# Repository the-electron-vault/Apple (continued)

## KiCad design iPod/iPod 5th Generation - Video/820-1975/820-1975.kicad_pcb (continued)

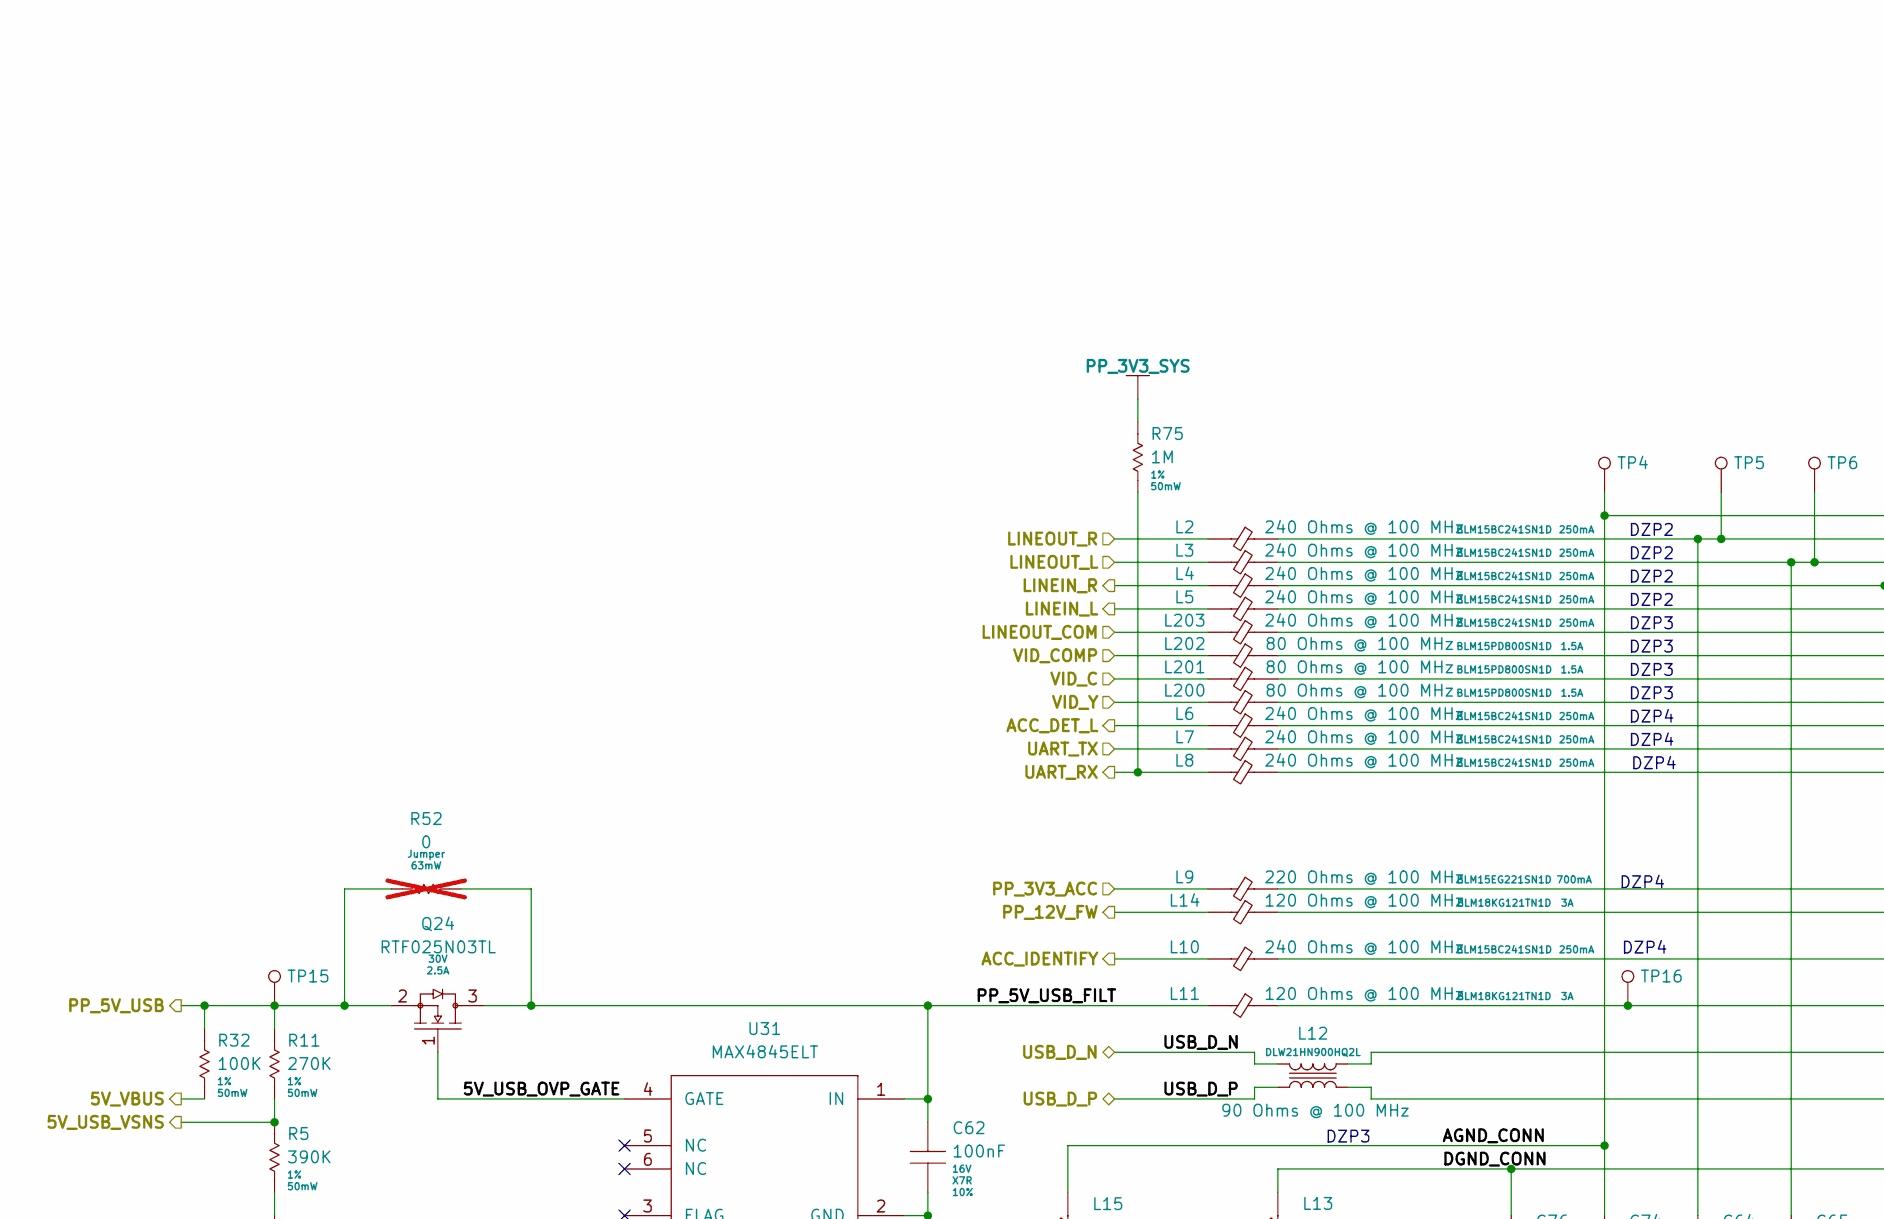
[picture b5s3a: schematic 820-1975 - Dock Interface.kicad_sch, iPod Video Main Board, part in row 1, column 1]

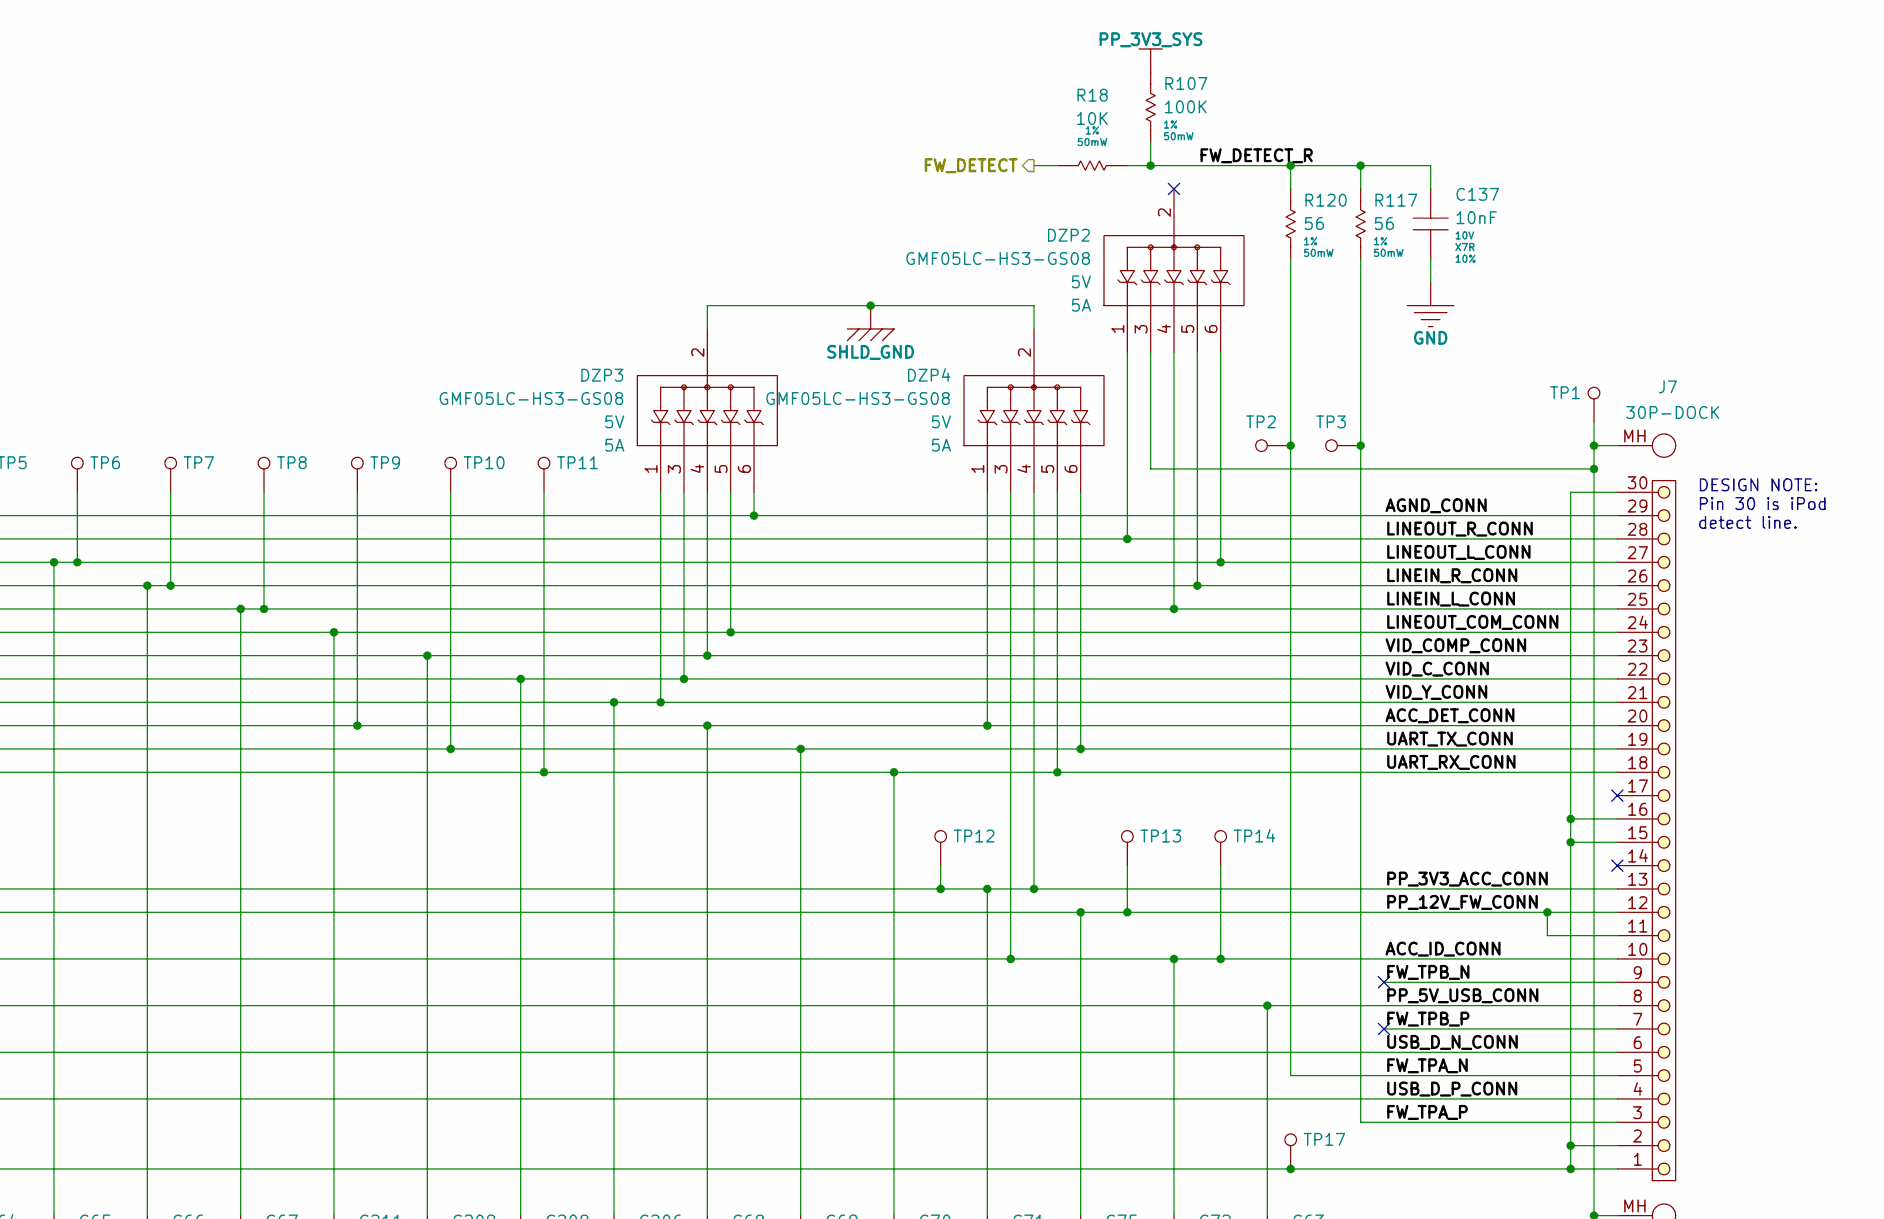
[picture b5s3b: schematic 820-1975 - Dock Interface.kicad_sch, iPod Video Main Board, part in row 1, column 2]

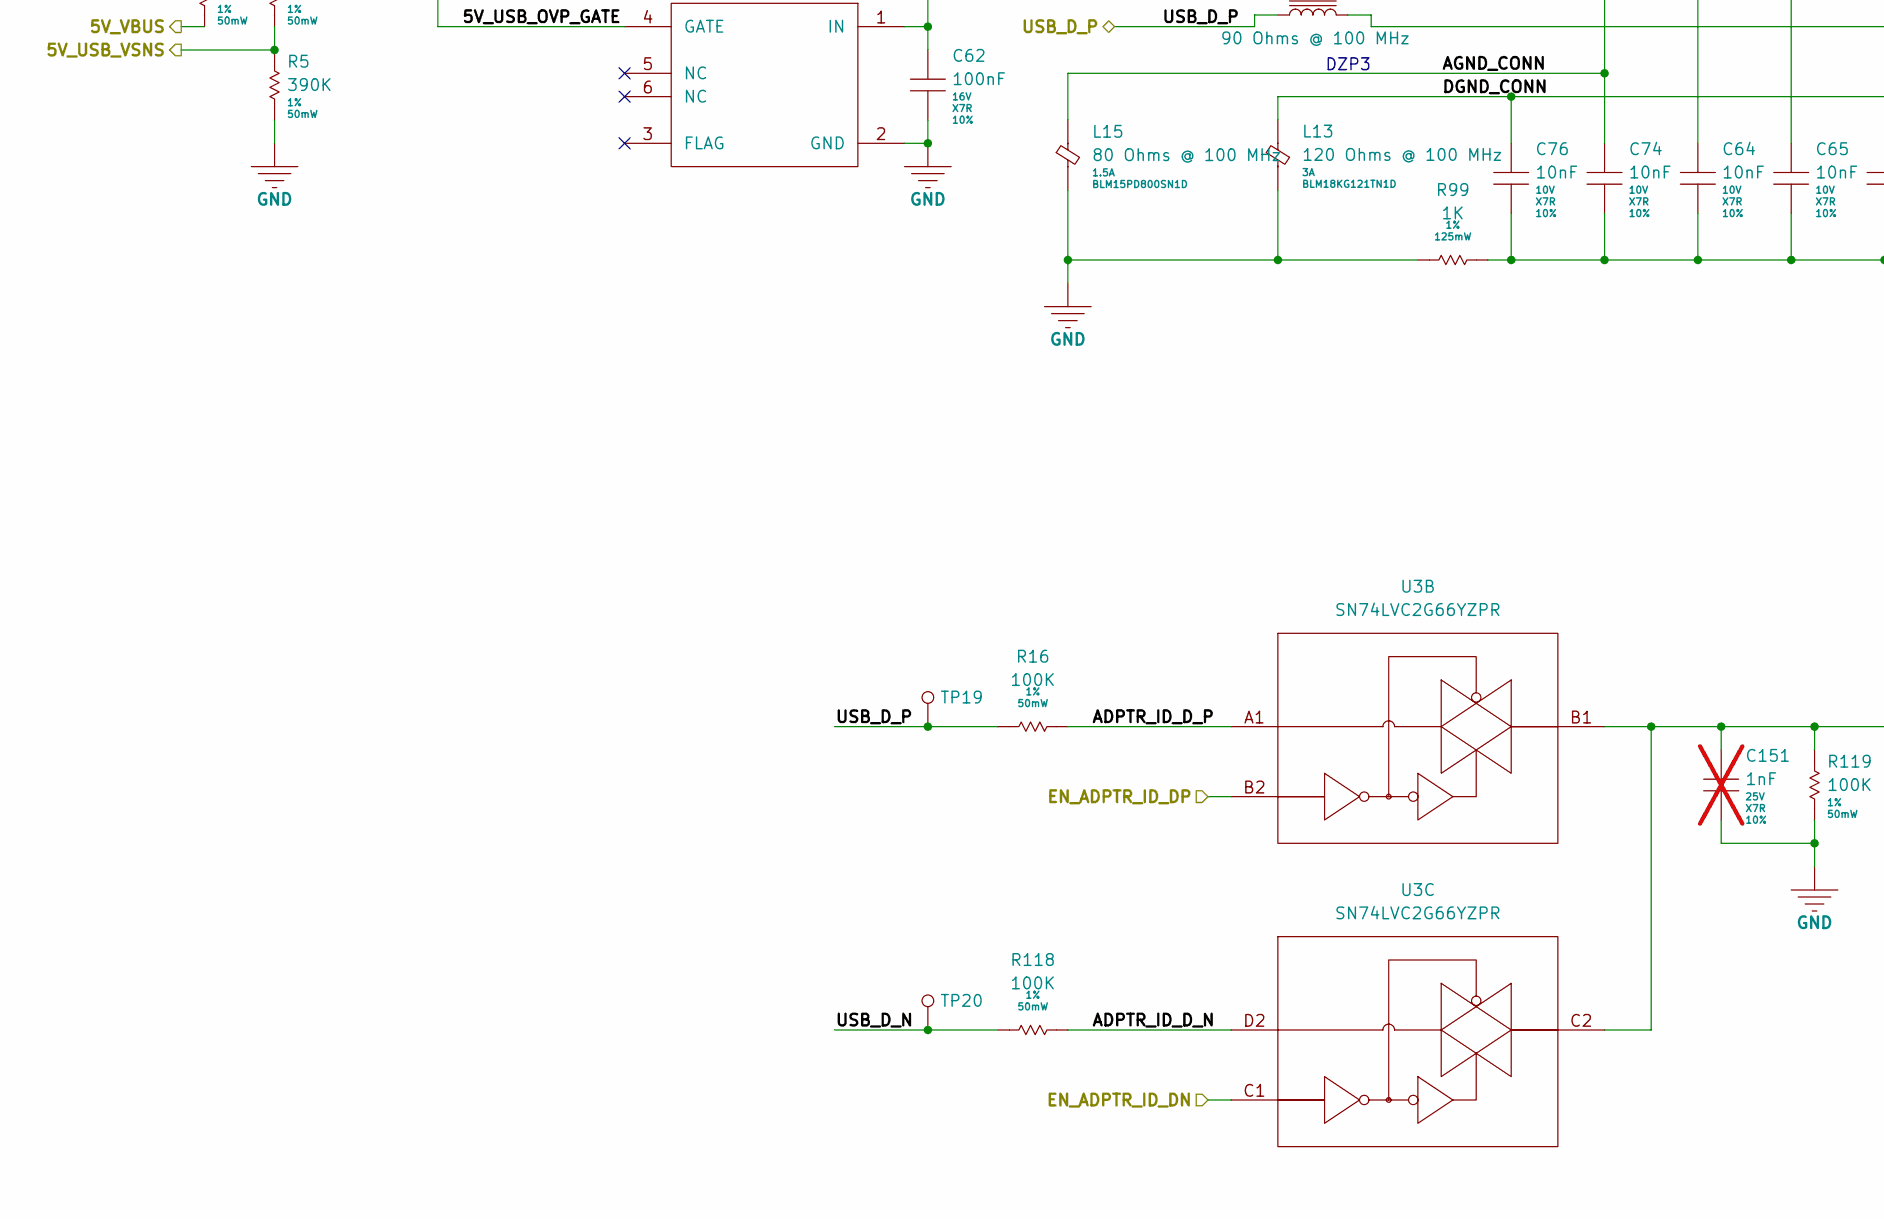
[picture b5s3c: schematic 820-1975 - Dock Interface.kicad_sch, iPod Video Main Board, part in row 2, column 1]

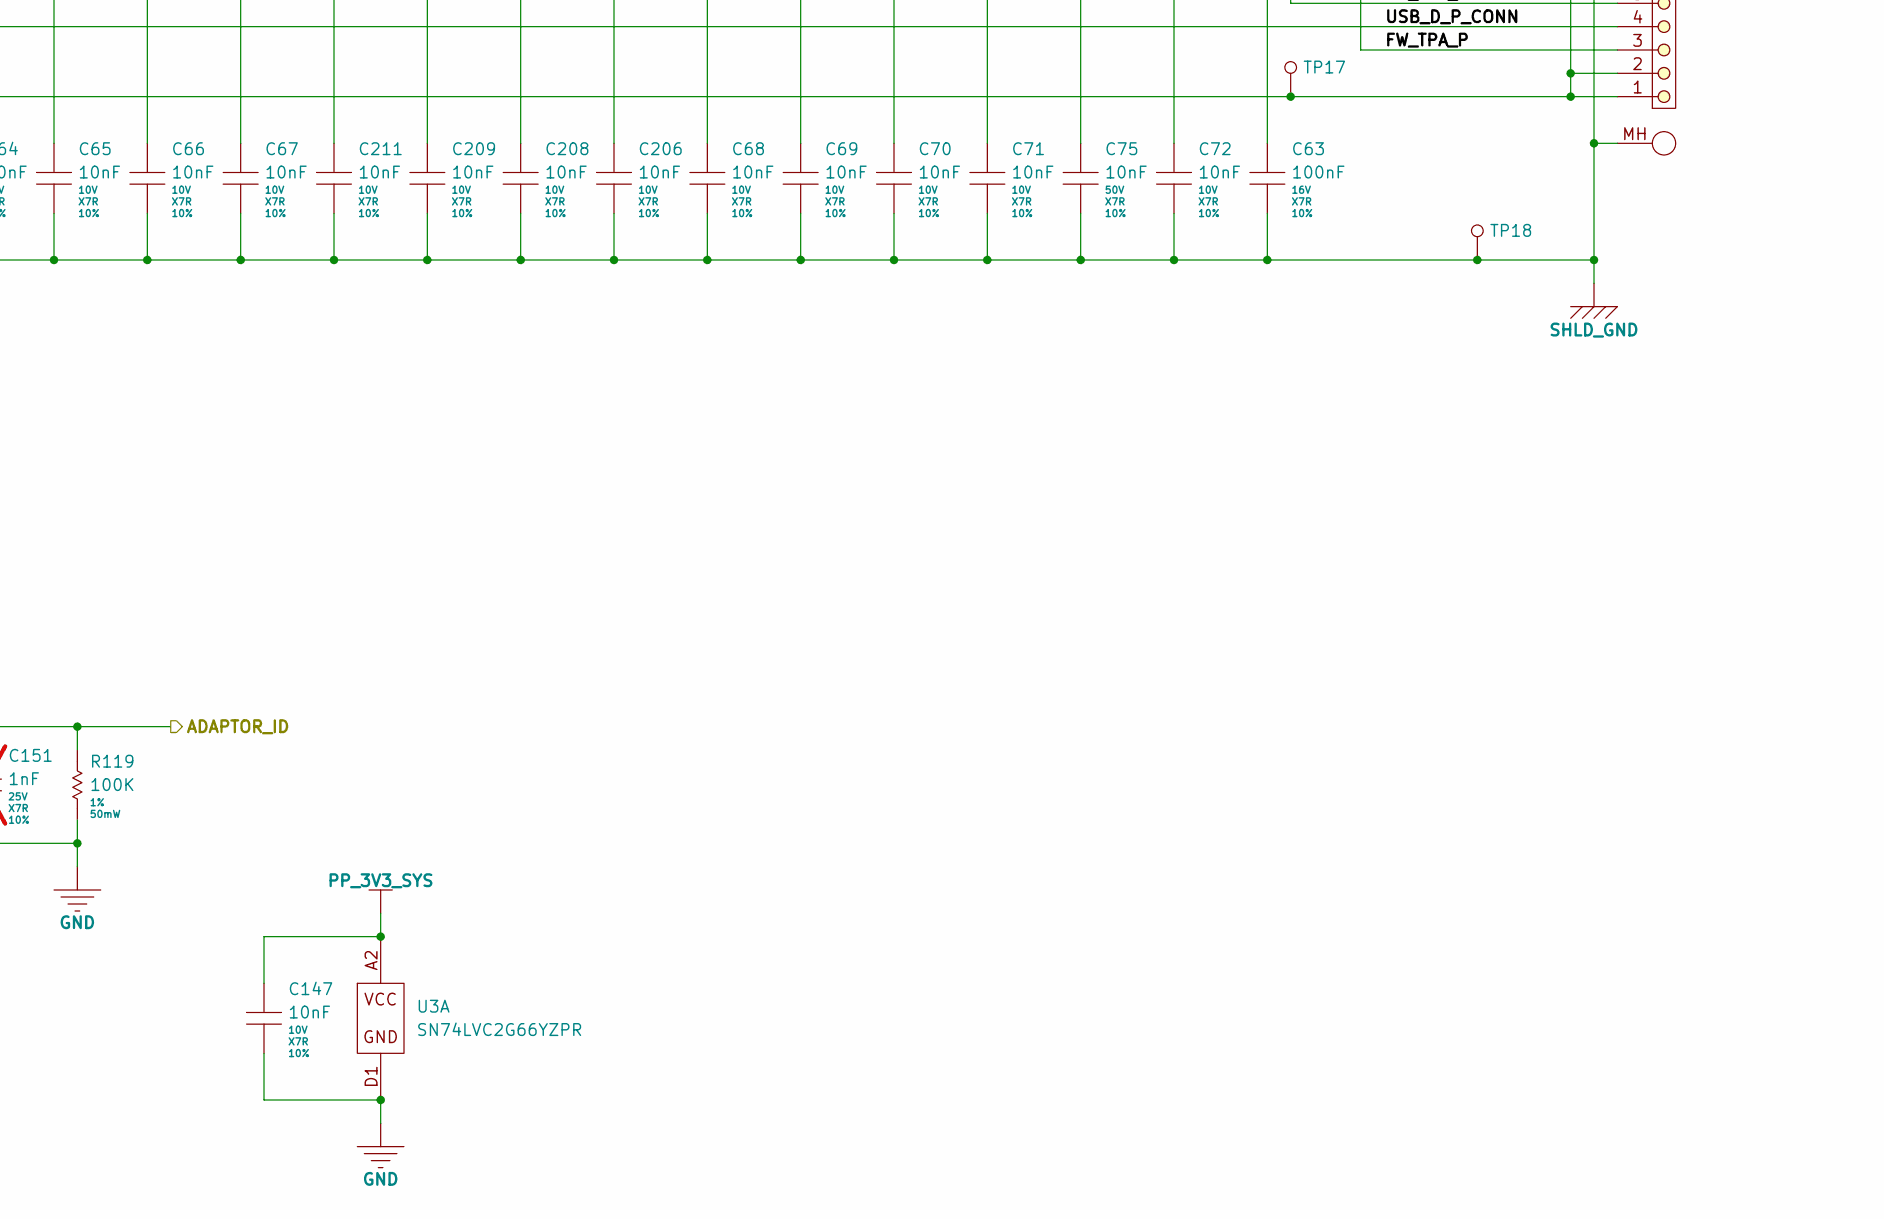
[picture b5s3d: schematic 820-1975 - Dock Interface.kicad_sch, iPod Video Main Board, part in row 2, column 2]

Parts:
C62, C63: 100nF; MLCC-0402; Voltage 16V; Tolerance 10%; Manufacturer Part Number GCM155R71C104KA55J
C64, C65, C66, C67, C68, C69, C70, C71, C72, C74, C76, C137, C147, C206, C208, C209, C211: 10nF; MLCC-0201; Voltage 10V; Tolerance 10%; Manufacturer Part Number GRM033R71A103KA01D
C75: 10nF; MLCC-0603; Voltage 50V; Tolerance 10%; Manufacturer Part Number GCM188R71H103KA37D
C151: 1nF; MLCC-0201; Voltage 25V; Tolerance 10%; Manufacturer Part Number GRM033R71E102KA01J; not fitted
DZP2, DZP3, DZP4: GMF05LC-HS3-GS08; VISHAY-LLP75-6A; Voltage 5V; Manufacturer Part Number GMF05LC-HS3-GS08
J7: 30P-DOCK; Manufacturer Part Number 30P-DOCK
L2, L3, L4, L5, L6, L7, L8, L10, L203: 240 Ohms @ 100 MHz; FB-0402; Manufacturer Part Number BLM15BC241SN1D
L9: 220 Ohms @ 100 MHz; FB-0402; Manufacturer Part Number BLM15EG221SN1D
L11, L13, L14: 120 Ohms @ 100 MHz; FB-0603; Manufacturer Part Number BLM18KG121TN1D
L12: 90 Ohms @ 100 MHz; DLW21HNxxxHQ; Manufacturer Part Number DLW21HN900HQ2L
L15, L200, L201, L202: 80 Ohms @ 100 MHz; FB-0402; Manufacturer Part Number BLM15PD800SN1D
Q24: RTF025N03TL; ROHM-SOT-323T; Voltage 30V; Manufacturer Part Number RTF025N03TL
R5: 390K; RES-0201; Tolerance 1%; Manufacturer Part Number CRCW0201390KFNED
R11: 270K; RES-0201; Tolerance 1%; Manufacturer Part Number CRCW0201270KFNED
R16, R32, R107, R118, R119: 100K; RES-0201; Tolerance 1%; Manufacturer Part Number CRCW0201100KFNED
R18: 10K; RES-0201; Tolerance 1%; Manufacturer Part Number CRCW020110K0FNED
R52: 0; RES-0402; Tolerance Jumper; Manufacturer Part Number CRCW04020000Z0ED; not fitted
R75: 1M; RES-0201; Tolerance 1%; Manufacturer Part Number CRCW02011M00FNED
R99: 1K; RES-0402; Tolerance 1%; Manufacturer Part Number CRCW04021K00FKED
R117, R120: 56; RES-0201; Tolerance 1%; Manufacturer Part Number CRCW020156R0FNED
TP1, TP2, TP3, TP4, TP5, TP6, TP7, TP8, TP9, TP10, TP11, TP12, TP13, TP14, TP15, TP16, TP17, TP18, TP19, TP20: TP; TP-SMT
U3: SN74LVC2G66YZPR; TI-R-XBGA-N8; Manufacturer Part Number SN74LVC2G66YZPR
U31: MAX4845ELT; MAXIM-6-uDFN; Manufacturer Part Number MAX4845ELT

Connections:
/CODEC/LINEIN_L: L4.1; also elsewhere on the board
/CODEC/LINEIN_R: L5.1; also elsewhere on the board
/CODEC/LINEOUT_COM: L203.1; also elsewhere on the board
/CODEC/LINEOUT_L: L3.1; also elsewhere on the board
/CODEC/LINEOUT_R: L2.1; also elsewhere on the board
/Charger-and-3.3V-Supply/PP_5V_USB: Q24.2 (S), R11.1, R32.1, R52.1, TP15.1; also elsewhere on the board
/Dock-Interface/5V_USB_OVP_GATE: Q24.1 (G), U31.4 (GATE)
/Dock-Interface/5V_USB_VSNS: R5.1, R11.2; also elsewhere on the board
/Dock-Interface/5V_VBUS: R32.2; also elsewhere on the board
/Dock-Interface/ACC_DET_CONN: C68.1, DZP4.1 (K1), J7.20, L6.2, TP9.1
/Dock-Interface/ACC_DET_L: L6.1; also elsewhere on the board
/Dock-Interface/ACC_IDENTIFY: L10.1; also elsewhere on the board
/Dock-Interface/ACC_ID_CONN: C72.1, DZP4.3 (K2), J7.10, L10.2, TP14.1
/Dock-Interface/ADAPTOR_ID: C151.1, R119.1, U3.B1 (1B), U3.C2 (2B); also elsewhere on the board
/Dock-Interface/ADPTR_ID_D_N: R118.2, U3.D2 (2A)
/Dock-Interface/ADPTR_ID_D_P: R16.2, U3.A1 (1A)
/Dock-Interface/AGND_CONN: C74.1, DZP3.6 (K5), J7.29, L15.2, TP4.1
/Dock-Interface/DGND_CONN: C76.1, J7.1, J7.2, J7.15, J7.16, J7.30, L13.1, TP17.1
/Dock-Interface/EN_ADPTR_ID_DN: U3.C1 (2C); also elsewhere on the board
/Dock-Interface/EN_ADPTR_ID_DP: U3.B2 (1C); also elsewhere on the board
/Dock-Interface/FW_DETECT: R18.1; also elsewhere on the board
/Dock-Interface/FW_DETECT_R: C137.1, R18.2, R107.2, R117.1, R120.1
/Dock-Interface/FW_TPA_N: J7.5, R120.2, TP2.1
/Dock-Interface/FW_TPA_P: J7.3, R117.2, TP3.1
/Dock-Interface/FW_TPB_N: J7.9
/Dock-Interface/FW_TPB_P: J7.7
/Dock-Interface/LINEIN_L_CONN: C67.1, DZP2.4 (K3), J7.25, L5.2, TP8.1
/Dock-Interface/LINEIN_R_CONN: C66.1, DZP2.5 (K4), J7.26, L4.2, TP7.1
/Dock-Interface/LINEOUT_COM_CONN: C211.1, DZP3.5 (K4), J7.24, L203.2
/Dock-Interface/LINEOUT_L_CONN: C65.1, DZP2.6 (K5), J7.27, L3.2, TP6.1
/Dock-Interface/LINEOUT_R_CONN: C64.1, DZP2.1 (K1), J7.28, L2.2, TP5.1
/Dock-Interface/PP_3V3_ACC: L9.1; also elsewhere on the board
/Dock-Interface/PP_3V3_ACC_CONN: C71.1, DZP4.4 (K3), J7.13, L9.2, TP12.1
/Dock-Interface/PP_5V_USB_CONN: C63.1, J7.8, L11.2, TP16.1
/Dock-Interface/PP_5V_USB_FILT: C62.1, L11.1, Q24.3 (D), R52.2, U31.1 (IN)
/Dock-Interface/PP_12V_FW: L14.1; also elsewhere on the board
/Dock-Interface/PP_12V_FW_CONN: C75.1, J7.11, J7.12, L14.2, TP13.1
/Dock-Interface/UART_RX: L8.1, R75.2; also elsewhere on the board
/Dock-Interface/UART_RX_CONN: C70.1, DZP4.5 (K4), J7.18, L8.2, TP11.1
/Dock-Interface/UART_TX: L7.1; also elsewhere on the board
/Dock-Interface/UART_TX_CONN: C69.1, DZP4.6 (K5), J7.19, L7.2, TP10.1
/Dock-Interface/USB_D_N: L12.1, R118.1, TP20.1; also elsewhere on the board
/Dock-Interface/USB_D_N_CONN: J7.6, L12.2
/Dock-Interface/USB_D_P: L12.4, R16.1, TP19.1; also elsewhere on the board
/Dock-Interface/USB_D_P_CONN: J7.4, L12.3
/Dock-Interface/VID_C: L201.1; also elsewhere on the board
/Dock-Interface/VID_COMP: L202.1; also elsewhere on the board
/Dock-Interface/VID_COMP_CONN: C209.1, DZP3.4 (K3), J7.23, L202.2
/Dock-Interface/VID_C_CONN: C208.1, DZP3.3 (K2), J7.22, L201.2
/Dock-Interface/VID_Y: L200.1; also elsewhere on the board
/Dock-Interface/VID_Y_CONN: C206.1, DZP3.1 (K1), J7.21, L200.2
GND: C62.2, C137.2, C147.2, C151.2, L13.2, L15.1, R5.2, R99.1, R119.2, U3.D1 (GND), U31.2 (GND); also elsewhere on the board
PP_3V3_SYS: C147.1, R75.1, R107.1, U3.A2 (VCC); also elsewhere on the board
SHLD_GND: C63.2, C64.2, C65.2, C66.2, C67.2, C68.2, C69.2, C70.2, C71.2, C72.2, C74.2, C75.2, C76.2, C206.2, C208.2, C209.2, C211.2, DZP2.3 (K2), DZP3.2 (A), DZP4.2 (A), J7.MH, R99.2, TP1.1, TP18.1

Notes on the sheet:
DESIGN NOTE: Pin 30 is iPod detect line.
DZP2
DZP4
DZP3

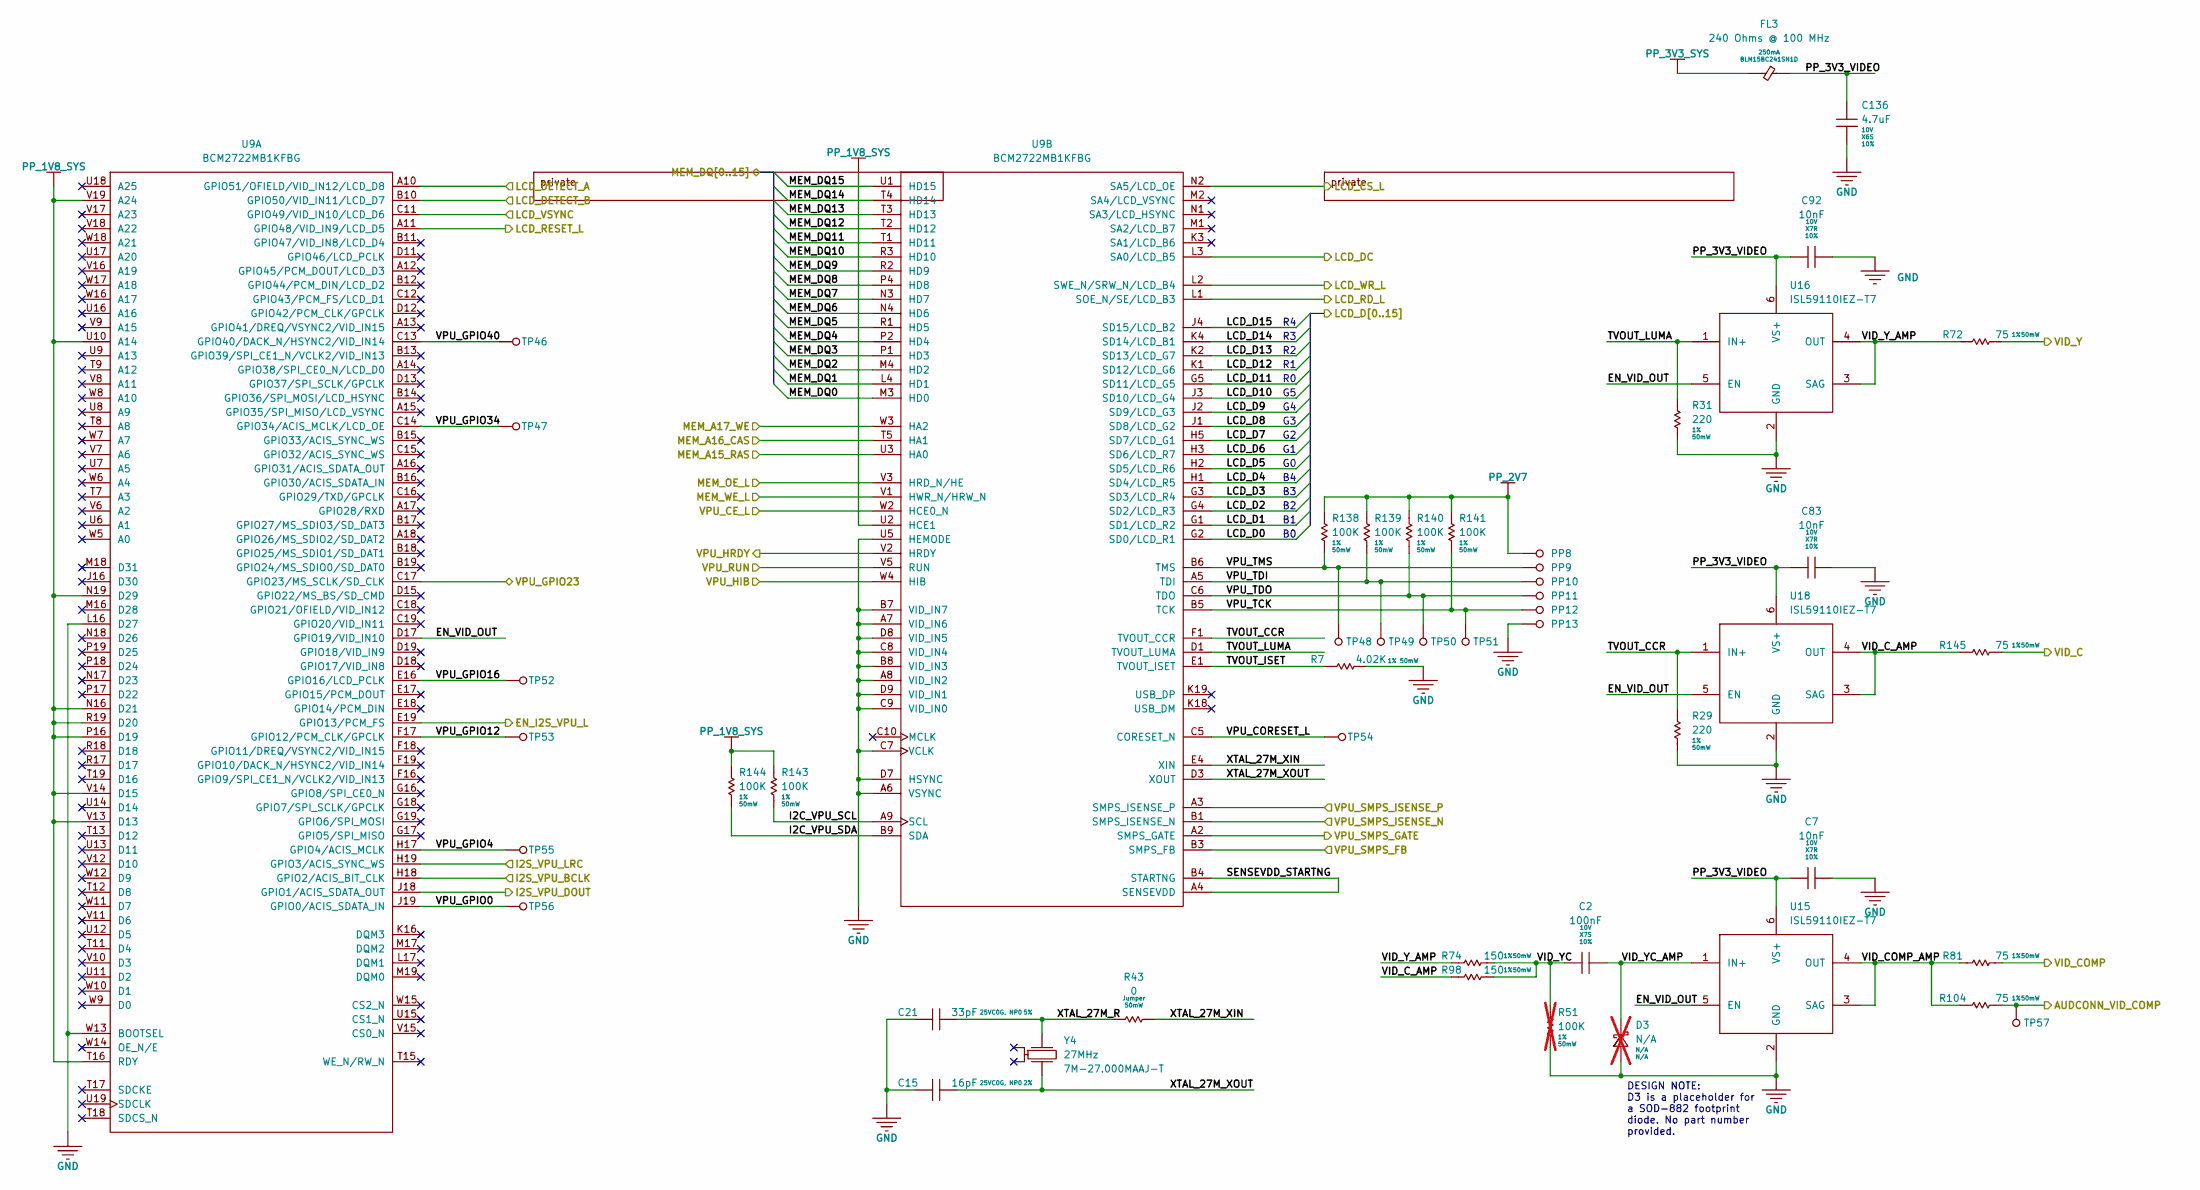
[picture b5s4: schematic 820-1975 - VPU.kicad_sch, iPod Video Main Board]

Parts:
C2: 100nF; MLCC-0201; Voltage 10V; Tolerance 10%; Manufacturer Part Number GRM033C71A104KE14D
C7, C83, C92: 10nF; MLCC-0201; Voltage 10V; Tolerance 10%; Manufacturer Part Number GRM033R71A103KA01D
C15: 16pF; MLCC-0201; Voltage 25V; Tolerance 2%; Manufacturer Part Number GRM0335C1E160GA01D
C21: 33pF; MLCC-0201; Voltage 25V; Tolerance 5%; Manufacturer Part Number GRM0335C1E330JA01D
C136: 4.7uF; MLCC-0603; Voltage 10V; Tolerance 10%; Manufacturer Part Number GRM188C71A475KE11D
D3: N/A; SOD-882; Voltage N/A; Manufacturer Part Number N/A; not fitted
FL3: 240 Ohms @ 100 MHz; FB-0402; Manufacturer Part Number BLM15BC241SN1D
PP8, PP9, PP10, PP11, PP12, PP13: TP; TP-SMT
R7: 4.02K; RES-0201; Tolerance 1%; Manufacturer Part Number CRCW02014K02FNED
R29, R31: 220; RES-0201; Tolerance 1%; Manufacturer Part Number CRCW0201220RFKED
R43: 0; RES-0201; Tolerance Jumper; Manufacturer Part Number CRCW02010000Z0ED
R51: 100K; RES-0201; Tolerance 1%; Manufacturer Part Number CRCW0201100KFNED; not fitted
R72, R81, R104, R145: 75; RES-0201; Tolerance 1%; Manufacturer Part Number CRCW020175R0FNED
R74, R98: 150; RES-0201; Tolerance 1%; Manufacturer Part Number CRCW0201150RFKED
R138, R139, R140, R141, R143, R144: 100K; RES-0201; Tolerance 1%; Manufacturer Part Number CRCW0201100KFNED
TP46, TP47, TP48, TP49, TP50, TP51, TP52, TP53, TP54, TP55, TP56, TP57: TP; TP-SMT
U9: BCM2722MB1KFBG; Manufacturer Part Number BCM2722MB1KFBG
U15, U16, U18: ISL59110IEZ-T7; ISL59110IEZ; Manufacturer Part Number ISL59110IEZ-T7
Y4: 27MHz; XTAL-3.2x2.5; Tolerance 30ppm; Manufacturer Part Number 7M-27.000MAAJ-T

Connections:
/CODEC/AUDCONN_VID_COMP: R104.2, TP57.1; also elsewhere on the board
/CODEC/EN_I2S_VPU_L: U9.E19 (GPIO13/PCM_FS); also elsewhere on the board
/CODEC/I2S_VPU_BCLK: U9.H18 (GPIO2/ACIS_BIT_CLK); also elsewhere on the board
/CODEC/I2S_VPU_DOUT: U9.J18 (GPIO1/ACIS_SDATA_OUT); also elsewhere on the board
/CODEC/I2S_VPU_LRC: U9.H19 (GPIO3/ACIS_SYNC_WS); also elsewhere on the board
/Dock-Interface/VID_C: R145.2; also elsewhere on the board
/Dock-Interface/VID_COMP: R81.2; also elsewhere on the board
/Dock-Interface/VID_Y: R72.2; also elsewhere on the board
/Flash-and-SDRAM/MEM_A15_RAS: U9.U3 (HA0); also elsewhere on the board
/Flash-and-SDRAM/MEM_A16_CAS: U9.T5 (HA1); also elsewhere on the board
/Flash-and-SDRAM/MEM_A17_WE: U9.W3 (HA2); also elsewhere on the board
/Flash-and-SDRAM/MEM_DQ0: U9.M3 (HD0); also elsewhere on the board
/Flash-and-SDRAM/MEM_DQ1: U9.L4 (HD1); also elsewhere on the board
/Flash-and-SDRAM/MEM_DQ2: U9.M4 (HD2); also elsewhere on the board
/Flash-and-SDRAM/MEM_DQ3: U9.P1 (HD3); also elsewhere on the board
/Flash-and-SDRAM/MEM_DQ4: U9.P2 (HD4); also elsewhere on the board
/Flash-and-SDRAM/MEM_DQ5: U9.R1 (HD5); also elsewhere on the board
/Flash-and-SDRAM/MEM_DQ6: U9.N4 (HD6); also elsewhere on the board
/Flash-and-SDRAM/MEM_DQ7: U9.N3 (HD7); also elsewhere on the board
/Flash-and-SDRAM/MEM_DQ8: U9.P4 (HD8); also elsewhere on the board
/Flash-and-SDRAM/MEM_DQ9: U9.R2 (HD9); also elsewhere on the board
/Flash-and-SDRAM/MEM_DQ10: U9.R3 (HD10); also elsewhere on the board
/Flash-and-SDRAM/MEM_DQ11: U9.T1 (HD11); also elsewhere on the board
/Flash-and-SDRAM/MEM_DQ12: U9.T2 (HD12); also elsewhere on the board
/Flash-and-SDRAM/MEM_DQ13: U9.T3 (HD13); also elsewhere on the board
/Flash-and-SDRAM/MEM_DQ14: U9.T4 (HD14); also elsewhere on the board
/Flash-and-SDRAM/MEM_DQ15: U9.U1 (HD15); also elsewhere on the board
/Flash-and-SDRAM/MEM_OE_L: U9.V3 (HRD_N/HE); also elsewhere on the board
/Flash-and-SDRAM/MEM_WE_L: U9.V1 (HWR_N/HRW_N); also elsewhere on the board
/LCD/LCD_CS_L: U9.N2 (SA5/LCD_OE); also elsewhere on the board
/LCD/LCD_D0: U9.G2 (SD0/LCD_R1); also elsewhere on the board
/LCD/LCD_D1: U9.G1 (SD1/LCD_R2); also elsewhere on the board
/LCD/LCD_D2: U9.G4 (SD2/LCD_R3); also elsewhere on the board
/LCD/LCD_D3: U9.G3 (SD3/LCD_R4); also elsewhere on the board
/LCD/LCD_D4: U9.H1 (SD4/LCD_R5); also elsewhere on the board
/LCD/LCD_D5: U9.H2 (SD5/LCD_R6); also elsewhere on the board
/LCD/LCD_D6: U9.H3 (SD6/LCD_R7); also elsewhere on the board
/LCD/LCD_D7: U9.H5 (SD7/LCD_G1); also elsewhere on the board
/LCD/LCD_D8: U9.J1 (SD8/LCD_G2); also elsewhere on the board
/LCD/LCD_D9: U9.J2 (SD9/LCD_G3); also elsewhere on the board
/LCD/LCD_D10: U9.J3 (SD10/LCD_G4); also elsewhere on the board
/LCD/LCD_D11: U9.G5 (SD11/LCD_G5); also elsewhere on the board
/LCD/LCD_D12: U9.K1 (SD12/LCD_G6); also elsewhere on the board
/LCD/LCD_D13: U9.K2 (SD13/LCD_G7); also elsewhere on the board
/LCD/LCD_D14: U9.K4 (SD14/LCD_B1); also elsewhere on the board
/LCD/LCD_D15: U9.J4 (SD15/LCD_B2); also elsewhere on the board
/LCD/LCD_DC: U9.L3 (SA0/LCD_B5); also elsewhere on the board
/LCD/LCD_RD_L: U9.L1 (SOE_N/SE/LCD_B3); also elsewhere on the board
/LCD/LCD_RESET_L: U9.A11 (GPIO48/VID_IN9/LCD_D5); also elsewhere on the board
/LCD/LCD_VSYNC: U9.C11 (GPIO49/VID_IN10/LCD_D6); also elsewhere on the board
/LCD/LCD_WR_L: U9.L2 (SWE_N/SRW_N/LCD_B4); also elsewhere on the board
/LCD_DETECT_A: U9.A10 (GPIO51/OFIELD/VID_IN12/LCD_D8); also elsewhere on the board
/LCD_DETECT_B: U9.B10 (GPIO50/VID_IN11/LCD_D7); also elsewhere on the board
/MPU/VPU_CE_L: U9.W2 (HCE0_N); also elsewhere on the board
/MPU/VPU_GPIO23: U9.C17 (GPIO23/MS_SCLK/SD_CLK); also elsewhere on the board
/MPU/VPU_HIB: U9.W4 (HIB); also elsewhere on the board
/MPU/VPU_HRDY: U9.V2 (HRDY); also elsewhere on the board
/MPU/VPU_RUN: U9.V5 (RUN); also elsewhere on the board
/VPU-Power/VPU_SMPS_FB: U9.B3 (SMPS_FB); also elsewhere on the board
/VPU-Power/VPU_SMPS_GATE: U9.A2 (SMPS_GATE); also elsewhere on the board
/VPU-Power/VPU_SMPS_ISENSE_N: U9.B1 (SMPS_ISENSE_N); also elsewhere on the board
/VPU/EN_VID_OUT: U9.D17 (GPIO19/VID_IN10), U15.5 (EN), U16.5 (EN), U18.5 (EN)
/VPU/I2C_VPU_SCL: R143.2, U9.A9 (SCL)
/VPU/I2C_VPU_SDA: R144.2, U9.B9 (SDA)
/VPU/PP_3V3_VIDEO: C7.1, C83.1, C92.1, C136.1, FL3.2, U15.6 (VS+), U16.6 (VS+), U18.6 (VS+)
/VPU/SENSEVDD_STARTNG: U9.A4 (SENSEVDD), U9.B4 (STARTNG)
/VPU/TVOUT_CCR: R29.1, U9.F1 (TVOUT_CCR), U18.1 (IN+)
/VPU/TVOUT_ISET: R7.1, U9.E1 (TVOUT_ISET)
/VPU/TVOUT_LUMA: R31.1, U9.D1 (TVOUT_LUMA), U16.1 (IN+)
/VPU/VID_COMP_AMP: R81.1, R104.1, U15.3 (SAG), U15.4 (OUT)
/VPU/VID_C_AMP: R98.1, R145.1, U18.3 (SAG), U18.4 (OUT)
/VPU/VID_YC: C2.1, R51.1, R74.2, R98.2
/VPU/VID_YC_AMP: C2.2, D3.K, U15.1 (IN+)
/VPU/VID_Y_AMP: R72.1, R74.1, U16.3 (SAG), U16.4 (OUT)
/VPU/VPU_CORESET_L: TP54.1, U9.C5 (CORESET_N)
/VPU/VPU_GPIO0: TP56.1, U9.J19 (GPIO0/ACIS_SDATA_IN)
/VPU/VPU_GPIO4: TP55.1, U9.H17 (GPIO4/ACIS_MCLK)
/VPU/VPU_GPIO12: TP53.1, U9.F17 (GPIO12/PCM_CLK/GPCLK)
/VPU/VPU_GPIO16: TP52.1, U9.E16 (GPIO16/LCD_PCLK)
/VPU/VPU_GPIO34: TP47.1, U9.C14 (GPIO34/ACIS_MCLK/LCD_OE)
/VPU/VPU_GPIO40: TP46.1, U9.C13 (GPIO40/DACK_N/HSYNC2/VID_IN14)
/VPU/VPU_TCK: PP12.1, R141.2, TP51.1, U9.B5 (TCK)
/VPU/VPU_TDI: PP10.1, R139.2, TP49.1, U9.A5 (TDI)
/VPU/VPU_TDO: PP11.1, R140.2, TP50.1, U9.C6 (TDO)
/VPU/VPU_TMS: PP9.1, R138.2, TP48.1, U9.B6 (TMS)
/VPU/XTAL_27M_R: C21.1, R43.1, Y4.1
/VPU/XTAL_27M_XIN: R43.2, U9.E4 (XIN)
/VPU/XTAL_27M_XOUT: C15.1, U9.D3 (XOUT), Y4.3
GND: C7.2, C15.2, C21.2, C83.2, C92.2, C136.2, D3.A, PP13.1, R7.2, R29.2, R31.2, R51.2, U9.A6 (VSYNC), U9.A7 (VID_IN6), U9.A8 (VID_IN2), U9.B7 (VID_IN7), U9.B8 (VID_IN3), U9.C7 (VCLK), U9.C8 (VID_IN4), U9.C9 (VID_IN0), U9.D7 (HSYNC), U9.D8 (VID_IN5), U9.D9 (VID_IN1), U9.L16 (D27), U9.U5 (HEMODE), U9.W13 (BOOTSEL), U15.2 (GND), U16.2 (GND), U18.2 (GND); also elsewhere on the board
PP_1V8_SYS: R143.1, R144.1, U9.N16 (D21), U9.N19 (D29), U9.P16 (D19), U9.R19 (D20), U9.T16 (RDY), U9.U2 (HCE1), U9.U10 (A14), U9.V13 (D13), U9.V14 (D15), U9.V19 (A24); also elsewhere on the board
PP_2V7: PP8.1, R138.1, R139.1, R140.1, R141.1; also elsewhere on the board
PP_3V3_SYS: FL3.1; also elsewhere on the board
PP_SYS_MAIN: U9.A3 (SMPS_ISENSE_P); also elsewhere on the board

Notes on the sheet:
DESIGN NOTE: D3 is a placeholder for a SOD-882 footprint diode. No part number provided.
